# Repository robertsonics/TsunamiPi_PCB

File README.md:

# TsunamiPi_PCB
8-Out 2-In Multichannel Audio HAT

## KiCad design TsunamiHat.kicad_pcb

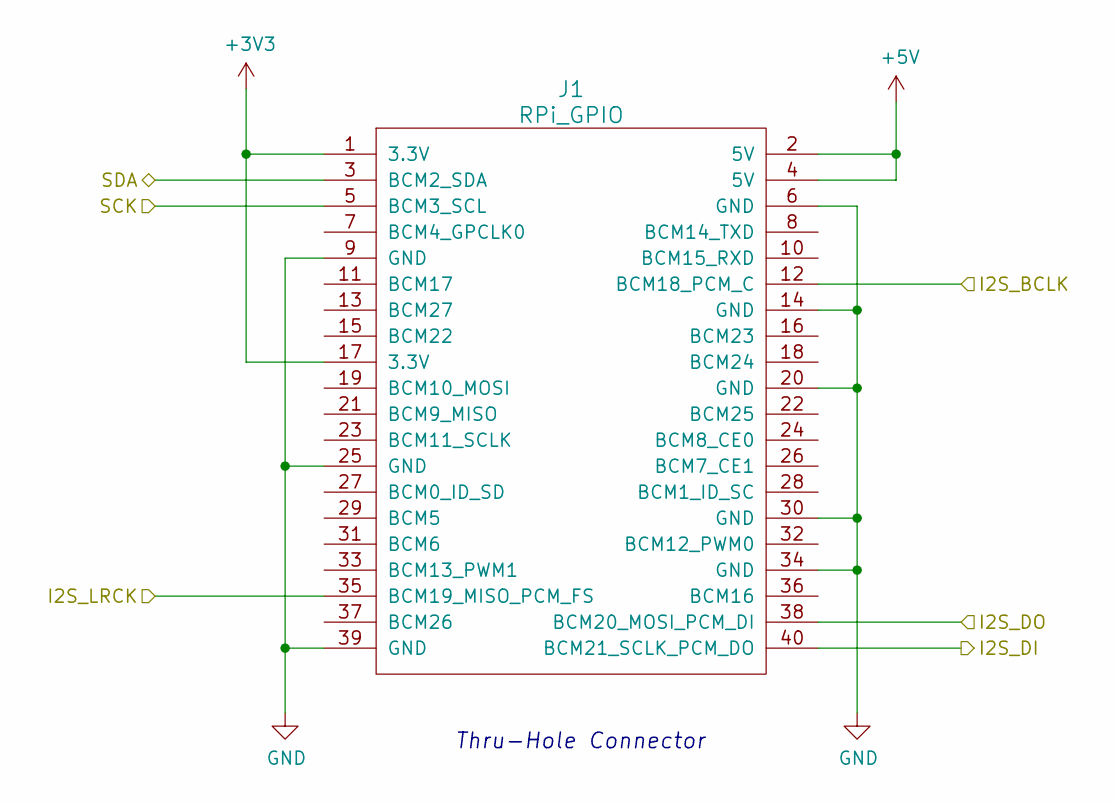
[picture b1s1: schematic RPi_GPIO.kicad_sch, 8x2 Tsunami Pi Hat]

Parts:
J1: RPi_GPIO; Pin_Header_Straight_2x20

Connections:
+3V3: J1.1 (3.3V), J1.17 (3.3V); also elsewhere on the board
+5V: J1.2 (5V), J1.4 (5V); also elsewhere on the board
/CPU/I2S_BCLK: J1.12 (BCM18_PCM_C); also elsewhere on the board
/CPU/I2S_DI: J1.40 (BCM21_SCLK_PCM_DO); also elsewhere on the board
/CPU/I2S_LRCK: J1.35 (BCM19_MISO_PCM_FS); also elsewhere on the board
/CPU/SCK: J1.5 (BCM3_SCL); also elsewhere on the board
/CPU/SDA: J1.3 (BCM2_SDA); also elsewhere on the board
/Codec/I2S_DO: J1.38 (BCM20_MOSI_PCM_DI); also elsewhere on the board
GND: J1.6 (GND), J1.9 (GND), J1.14 (GND), J1.20 (GND), J1.25 (GND), J1.30 (GND), J1.34 (GND), J1.39 (GND); also elsewhere on the board

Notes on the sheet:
Thru-Hole Connector

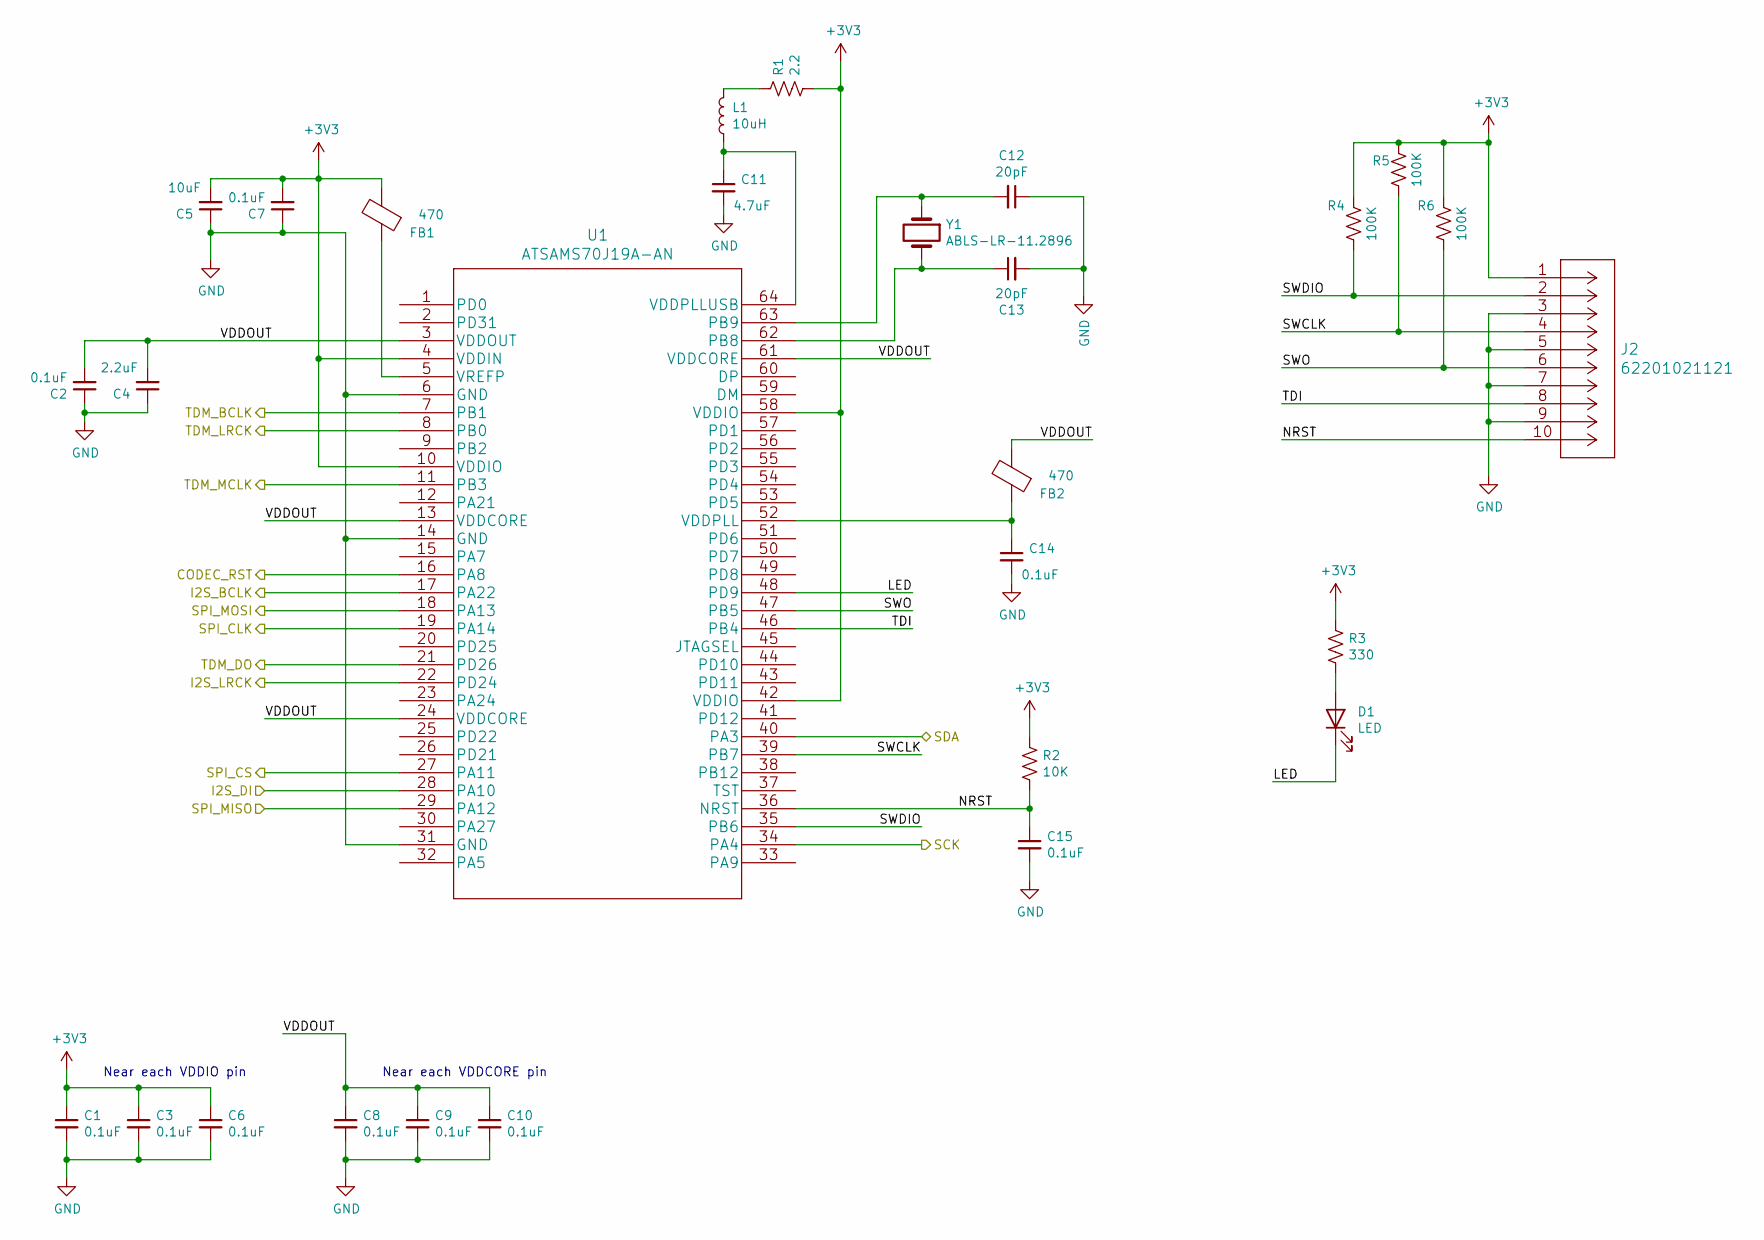
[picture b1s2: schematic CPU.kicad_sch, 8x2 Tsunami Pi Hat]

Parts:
C1, C2, C3, C6, C7, C8, C9, C10, C14, C15: 0.1uF; C_0603_1608Metric
C4: 2.2uF; C_0603_1608Metric
C5: 10uF; C_0805_2012Metric
C11: 4.7uF; C_0603_1608Metric
C12, C13: 20pF; C_0603_1608Metric
D1: LED; LED_0603_1608Metric
FB1, FB2: 470; L_0603_1608Metric
J2: 62201021121
L1: 10uH; L_0603_1608Metric
R1: 2.2; R_0603_1608Metric
R2: 10K; R_0603_1608Metric
R3: 330; R_0603_1608Metric
R4, R5, R6: 100K; R_0603_1608Metric
U1: ATSAMS70J19A-AN
Y1: ABLS-LR-11.2896; XTAL_ABLS-24.000MHZ-B4-T

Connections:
+3V3: C1.1, C3.1, C5.2, C6.1, C7.2, FB1.2, J2.1, R1.1, R2.2, R3.2, R4.2, R5.2, R6.2, U1.4 (VDDIN), U1.10 (VDDIO), U1.42 (VDDIO), U1.58 (VDDIO); also elsewhere on the board
/CPU/CODEC_RST: U1.16 (PA8); also elsewhere on the board
/CPU/I2S_BCLK: U1.17 (PA22); also elsewhere on the board
/CPU/I2S_DI: U1.28 (PA10); also elsewhere on the board
/CPU/I2S_LRCK: U1.22 (PD24); also elsewhere on the board
/CPU/LED: D1.1 (K), U1.48 (PD9)
/CPU/NRST: C15.1, J2.10, R2.1, U1.36 (NRST)
/CPU/SCK: U1.34 (PA4); also elsewhere on the board
/CPU/SDA: U1.40 (PA3); also elsewhere on the board
/CPU/SPI_CLK: U1.19 (PA14); also elsewhere on the board
/CPU/SPI_CS: U1.27 (PA11); also elsewhere on the board
/CPU/SPI_MISO: U1.29 (PA12); also elsewhere on the board
/CPU/SPI_MOSI: U1.18 (PA13); also elsewhere on the board
/CPU/SWCLK: J2.4, R5.1, U1.39 (PB7)
/CPU/SWDIO: J2.2, R4.1, U1.35 (PB6)
/CPU/SWO: J2.6, R6.1, U1.47 (PB5)
/CPU/TDI: J2.8, U1.46 (PB4)
/CPU/TDM_BCLK: U1.7 (PB1); also elsewhere on the board
/CPU/TDM_DO: U1.21 (PD26); also elsewhere on the board
/CPU/TDM_LRCK: U1.8 (PB0); also elsewhere on the board
/CPU/TDM_MCLK: U1.11 (PB3); also elsewhere on the board
/CPU/VDDOUT: C2.2, C4.2, C8.1, C9.1, C10.1, FB2.2, U1.3 (VDDOUT), U1.13 (VDDCORE), U1.24 (VDDCORE), U1.61 (VDDCORE)
GND: C1.2, C2.1, C3.2, C4.1, C5.1, C6.2, C7.1, C8.2, C9.2, C10.2, C11.2, C12.1, C13.2, C14.2, C15.2, J2.3, J2.5, J2.7, J2.9, U1.6 (GND), U1.14 (GND), U1.31 (GND); also elsewhere on the board
unnamed: C11.1, L1.1, U1.64 (VDDPLLUSB)
unnamed: C12.2, U1.63 (PB9), Y1.1
unnamed: C13.1, U1.62 (PB8), Y1.2
unnamed: C14.1, FB2.1, U1.52 (VDDPLL)
unnamed: D1.2 (A), R3.1
unnamed: FB1.1, U1.5 (VREFP)
unnamed: L1.2, R1.2

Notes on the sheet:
Near each VDDCORE pin
Near each VDDIO pin

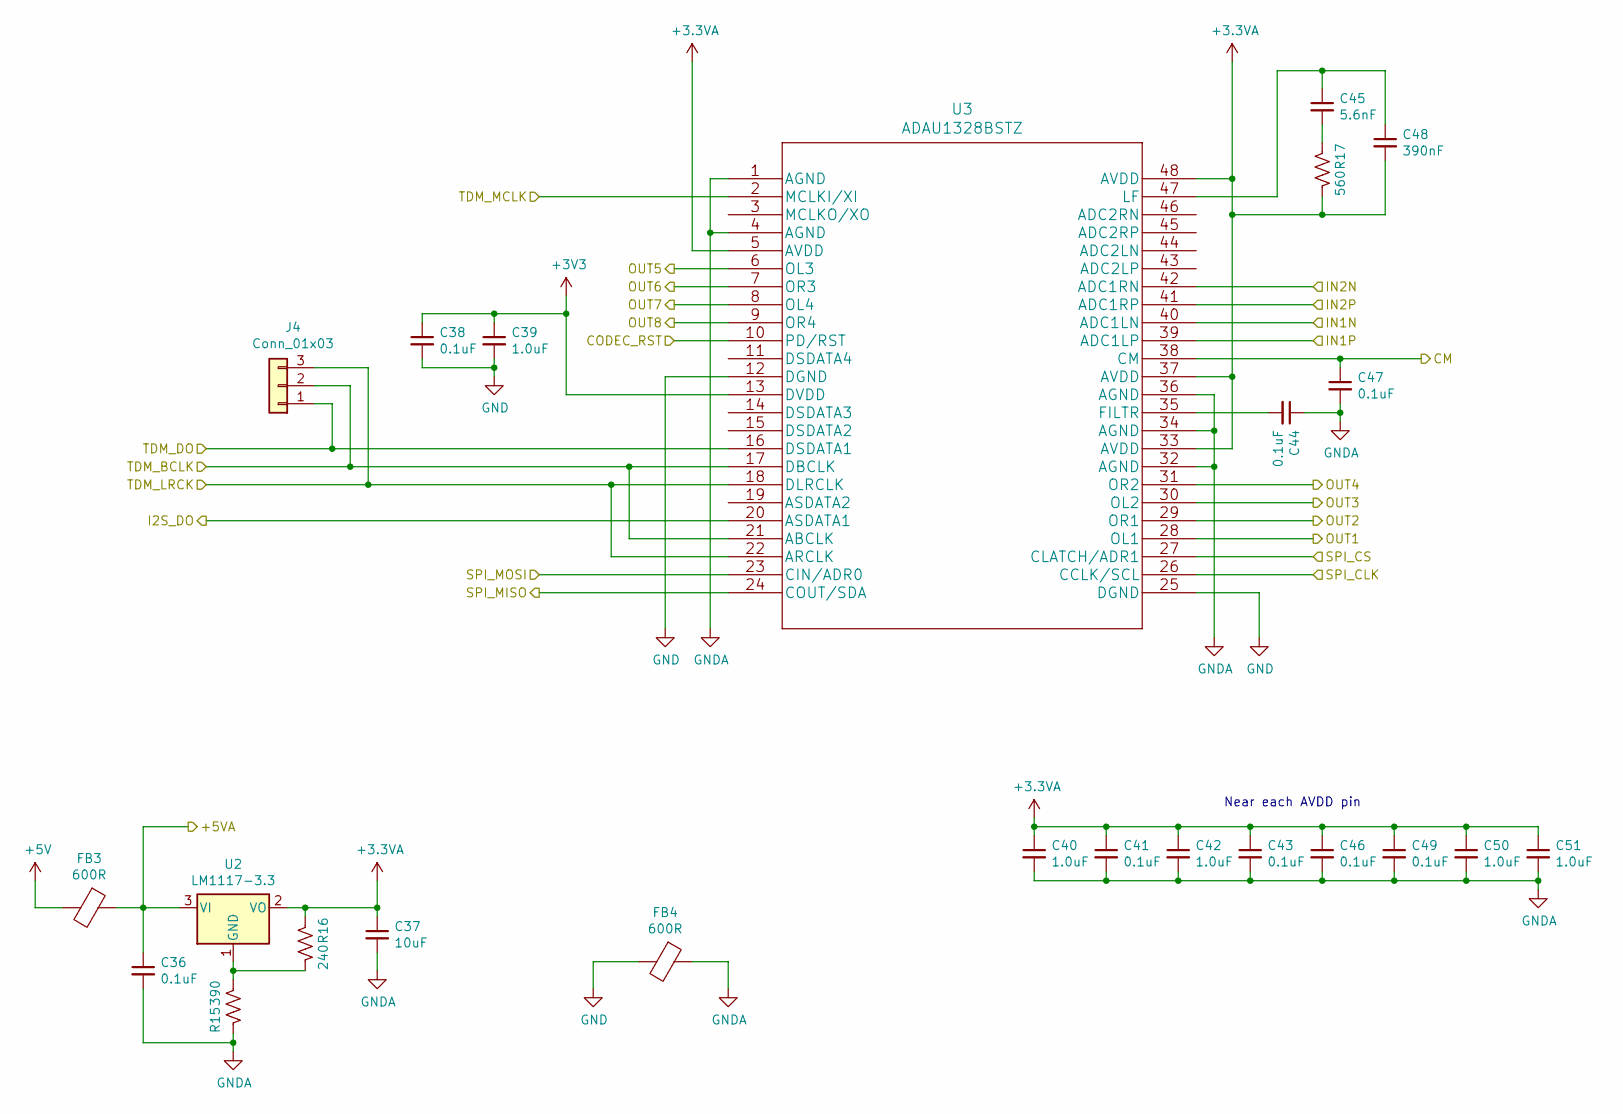
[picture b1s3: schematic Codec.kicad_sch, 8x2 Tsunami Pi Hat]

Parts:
C36, C38, C41, C43, C44, C46, C47, C49: 0.1uF; C_0603_1608Metric
C37: 10uF; C_0805_2012Metric
C39, C40, C42, C50, C51: 1.0uF; C_0603_1608Metric
C45: 5.6nF; C_0603_1608Metric
C48: 390nF; C_0603_1608Metric
FB3, FB4: 600R; L_0603_1608Metric
J4: Conn_01x03; PinHeader_1x03_P2.54mm_Vertical
R15: 390; R_0603_1608Metric
R16: 240; R_0603_1608Metric
R17: 560; R_0603_1608Metric
U2: LM1117-3.3; SOT-223-3_TabPin2; Mpn LM1117MP-3.3/NOPB
U3: ADAU1328BSTZ

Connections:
+3.3VA: C37.1, C40.1, C41.1, C42.1, C43.1, C46.1, C48.2, C49.1, C50.1, C51.1, R16.2, R17.1, U2.2 (VO), U3.5 (AVDD), U3.33 (AVDD), U3.37 (AVDD), U3.48 (AVDD); also elsewhere on the board
+3V3: C38.1, C39.1, U3.13 (DVDD); also elsewhere on the board
+5V: FB3.2; also elsewhere on the board
/AnalogIO/CM: C47.1, U3.38 (CM); also elsewhere on the board
/AnalogIO/IN1N: U3.40 (ADC1LN); also elsewhere on the board
/AnalogIO/IN1P: U3.39 (ADC1LP); also elsewhere on the board
/AnalogIO/IN2N: U3.42 (ADC1RN); also elsewhere on the board
/AnalogIO/IN2P: U3.41 (ADC1RP); also elsewhere on the board
/AnalogIO/OUT1: U3.28 (OL1); also elsewhere on the board
/AnalogIO/OUT2: U3.29 (OR1); also elsewhere on the board
/AnalogIO/OUT3: U3.30 (OL2); also elsewhere on the board
/AnalogIO/OUT4: U3.31 (OR2); also elsewhere on the board
/AnalogIO/OUT5: U3.6 (OL3); also elsewhere on the board
/AnalogIO/OUT6: U3.7 (OR3); also elsewhere on the board
/AnalogIO/OUT7: U3.8 (OL4); also elsewhere on the board
/AnalogIO/OUt8: U3.9 (OR4); also elsewhere on the board
/CPU/CODEC_RST: U3.10 (PD/RST); also elsewhere on the board
/CPU/SPI_CLK: U3.26 (CCLK/SCL); also elsewhere on the board
/CPU/SPI_CS: U3.27 (CLATCH/ADR1); also elsewhere on the board
/CPU/SPI_MISO: U3.24 (COUT/SDA); also elsewhere on the board
/CPU/SPI_MOSI: U3.23 (CIN/ADR0); also elsewhere on the board
/CPU/TDM_BCLK: J4.2, U3.17 (DBCLK), U3.21 (ABCLK); also elsewhere on the board
/CPU/TDM_DO: J4.1, U3.16 (DSDATA1); also elsewhere on the board
/CPU/TDM_LRCK: J4.3, U3.18 (DLRCLK), U3.22 (ARCLK); also elsewhere on the board
/CPU/TDM_MCLK: U3.2 (MCLKI/XI); also elsewhere on the board
/Codec/+5VA: C36.1, FB3.1, U2.3 (VI)
/Codec/I2S_DO: U3.20 (ASDATA1); also elsewhere on the board
GND: C38.2, C39.2, FB4.2, U3.12 (DGND), U3.25 (DGND); also elsewhere on the board
GNDA: C36.2, C37.2, C40.2, C41.2, C42.2, C43.2, C44.1, C46.2, C47.2, C49.2, C50.2, C51.2, FB4.1, R15.2, U3.1 (AGND), U3.4 (AGND), U3.32 (AGND), U3.34 (AGND), U3.36 (AGND); also elsewhere on the board
unnamed: C44.2, U3.35 (FILTR)
unnamed: C45.1, C48.1, U3.47 (LF)
unnamed: C45.2, R17.2
unnamed: R15.1, R16.1, U2.1 (GND)

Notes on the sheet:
Near each AVDD pin

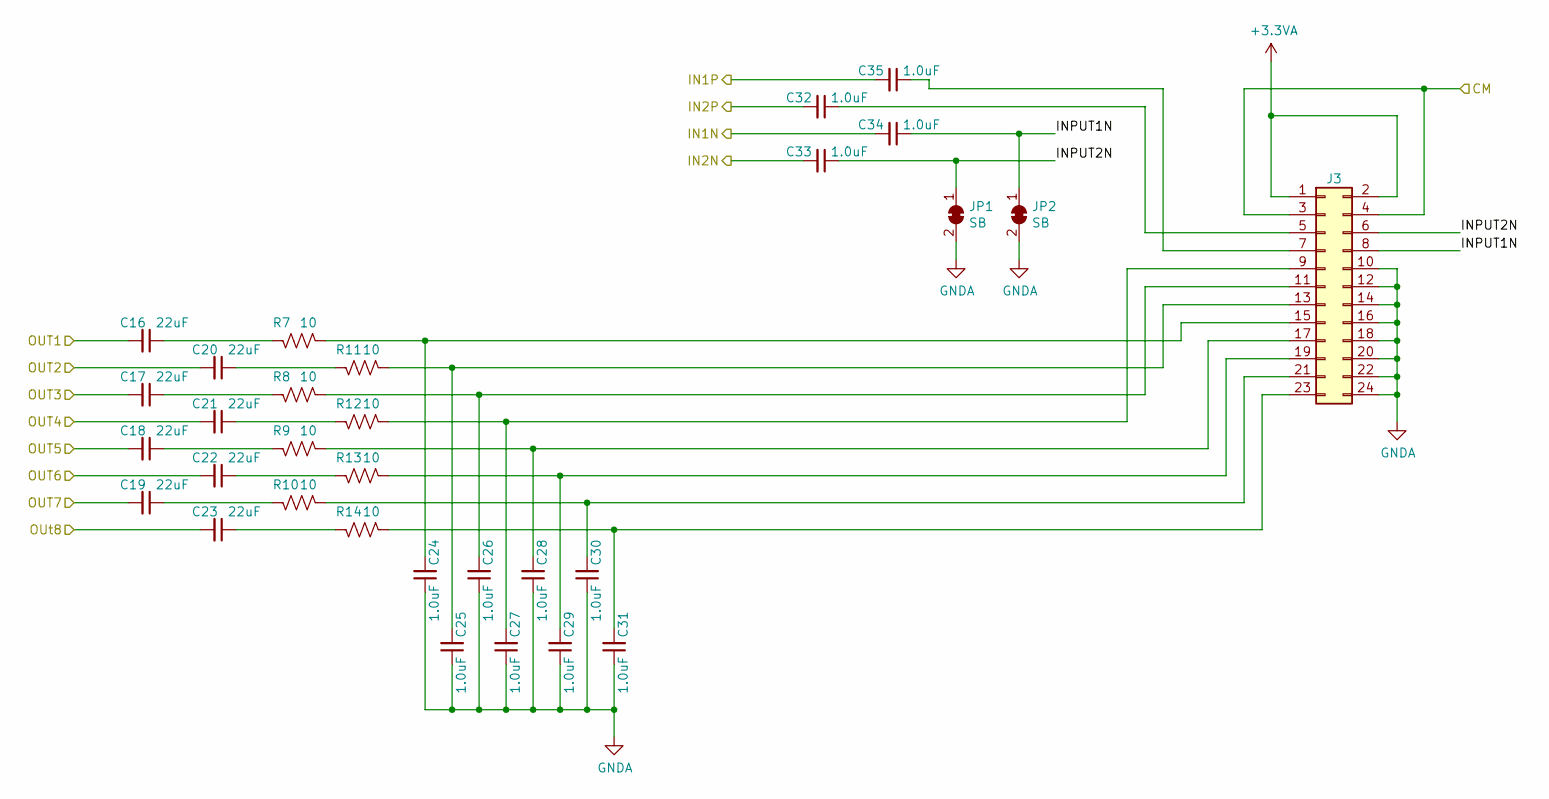
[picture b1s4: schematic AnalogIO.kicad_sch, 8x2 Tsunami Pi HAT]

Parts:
C16, C17, C18, C19, C20, C21, C22, C23: 22uF; C_0805_2012Metric
C24, C25, C26, C27, C28, C29, C30, C31, C32, C33, C34, C35: 1.0uF; C_0603_1608Metric
J3: Conn_02x12_Odd_Even; PinHeader_2x12_P2.54mm_Vertical
JP1, JP2: SB; SolderJumper-2_P1.3mm_Bridged_RoundedPad1.0x1.5mm
R7, R8, R9, R10, R11, R12, R13, R14: 10; R_0603_1608Metric

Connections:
+3.3VA: J3.1, J3.2; also elsewhere on the board
/AnalogIO/CM: J3.3, J3.4; also elsewhere on the board
/AnalogIO/IN1N: C34.2; also elsewhere on the board
/AnalogIO/IN1P: C35.2; also elsewhere on the board
/AnalogIO/IN2N: C33.2; also elsewhere on the board
/AnalogIO/IN2P: C32.2; also elsewhere on the board
/AnalogIO/INPUT1N: C34.1, J3.8, JP2.1 (A)
/AnalogIO/INPUT2N: C33.1, J3.6, JP1.1 (A)
/AnalogIO/OUT1: C16.2; also elsewhere on the board
/AnalogIO/OUT2: C20.2; also elsewhere on the board
/AnalogIO/OUT3: C17.2; also elsewhere on the board
/AnalogIO/OUT4: C21.2; also elsewhere on the board
/AnalogIO/OUT5: C18.2; also elsewhere on the board
/AnalogIO/OUT6: C22.2; also elsewhere on the board
/AnalogIO/OUT7: C19.2; also elsewhere on the board
/AnalogIO/OUt8: C23.2; also elsewhere on the board
GNDA: C24.1, C25.1, C26.1, C27.1, C28.1, C29.1, C30.1, C31.1, J3.10, J3.12, J3.14, J3.16, J3.18, J3.20, J3.22, J3.24, JP1.2 (B), JP2.2 (B); also elsewhere on the board
unnamed: C16.1, R7.2
unnamed: C17.1, R8.2
unnamed: C18.1, R9.2
unnamed: C19.1, R10.2
unnamed: C20.1, R11.2
unnamed: C21.1, R12.2
unnamed: C22.1, R13.2
unnamed: C23.1, R14.2
unnamed: C24.2, J3.15, R7.1
unnamed: C25.2, J3.13, R11.1
unnamed: C26.2, J3.11, R8.1
unnamed: C27.2, J3.9, R12.1
unnamed: C28.2, J3.17, R9.1
unnamed: C29.2, J3.19, R13.1
unnamed: C30.2, J3.21, R10.1
unnamed: C31.2, J3.23, R14.1
unnamed: C32.1, J3.5
unnamed: C35.1, J3.7

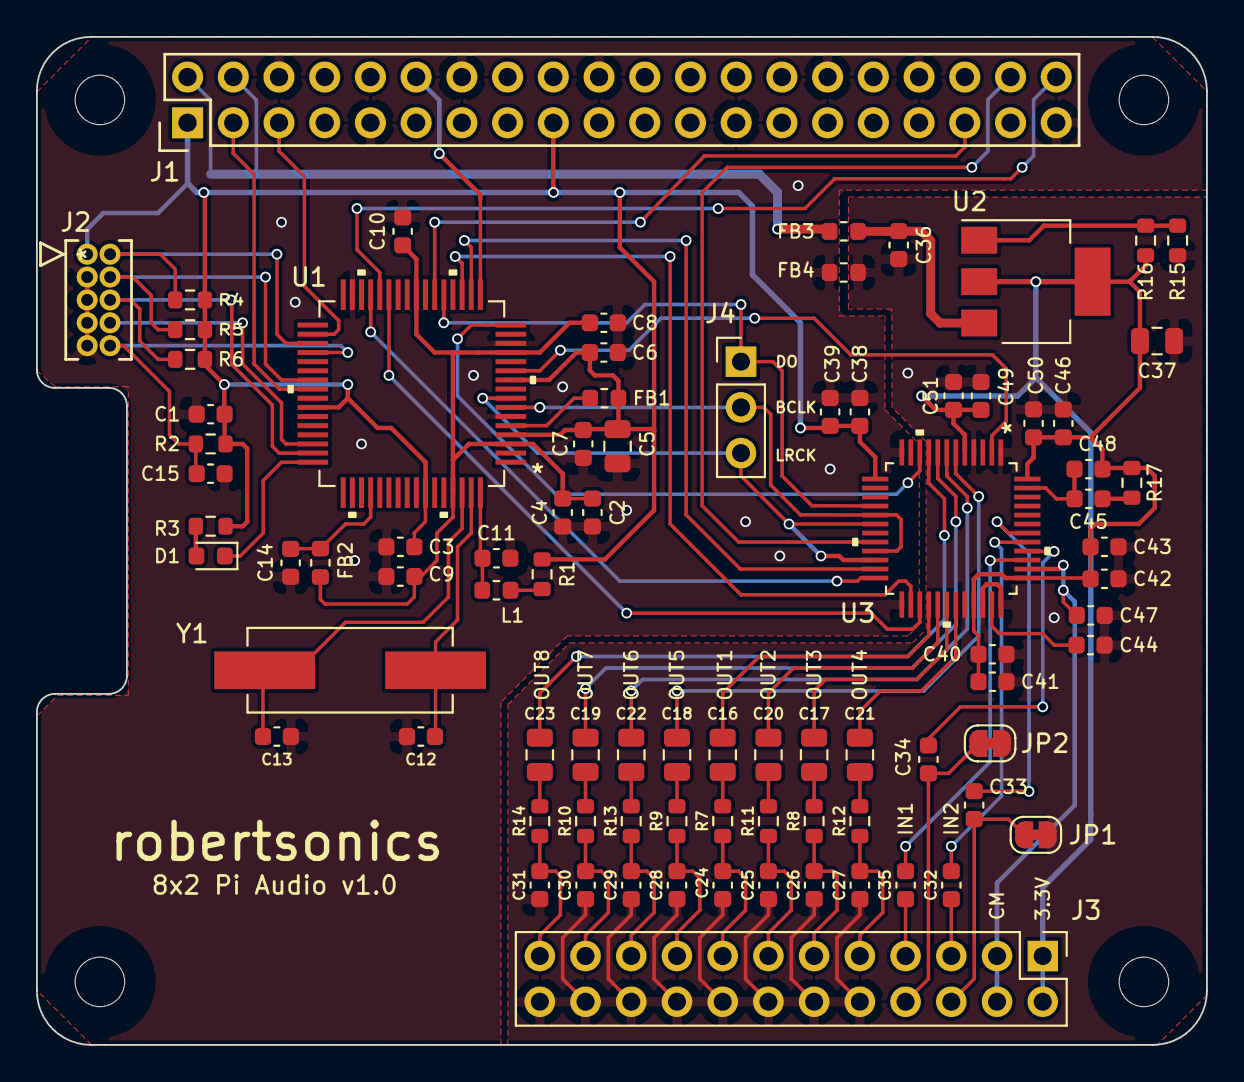
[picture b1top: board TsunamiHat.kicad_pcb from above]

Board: 2 copper layers, 65.0 x 56.0 mm, 84 parts (0 on the bottom side), 72 nets.

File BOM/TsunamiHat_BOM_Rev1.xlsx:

Item # | Quantity Per Board | Manufacturer Part # | Manufacturer | Do Not Install | Reference | Vendor | Vendor Part # | Value | Footprint
1 | 1 | CC0603MRX5R6BB475 |  |  | C11 | Digikey | 311-1820-1-ND | 4.7uF | 0603_1608Metric
2 | 2 | CBR06C200FAGAC |  |  | C12 C13 | Digikey | 399-8840-1-ND | 20pF | 0603_1608Metric
3 | 18 | C0603C104K9PAC7867 |  |  | C1 C2 C3 C6 C7 C8 C9 C10 C14 C15 C36 C38 C41 C43 C44 C46 C47 C49 | Digikey | 399-17575-1-ND | 0.1uF | 0603_1608Metric
4 | 8 | TACR226K006XTA |  |  | C16 C17 C18 C19 C20 C21 C22 C23 | Digikey | 478-4188-1-ND | 22uF | 0805_2012Metric
5 | 17 | C0603C105K4PACTU |  |  | C24 C25 C26 C27 C28 C29 C30 C31 C32 C33 C34 C35 C39 C40 C42 C50 C51 | Digikey | 399-5090-1-ND | 1.0uF | 0603_1608Metric
6 | 1 | C0603C225K8PACTU |  |  | C4 | Digikey | 399-4911-1-ND | 2.2uF | 0603_1608Metric
7 | 1 | 06035C562JAT2A |  |  | C45 | Digikey | 478-12728-1-ND | 5.6nF | 0603_1608Metric
8 | 1 | C0603C394J4RAC7867 |  |  | C48 | Digikey | 399-17256-1-ND | 390nF | 0603_1608Metric
9 | 2 | CC0805KRX5R6BB106 |  |  | C5 C37 | Digikey | 311-3424-1-ND | 10uF | 0805_2012Metric
10 | 1 | LTST-C191TBKT | LITEON |  | D1 | Digikey | 160-1647-1-ND | LED | 0603_1608Metric
11 | 2 | FBMH1608HL471-T | Taiyo Yuden |  | FB1 FB2 | Digikey | 587-1735-1-ND | 470 | 0603_1608Metric
12 | 2 | KPZ1608SHR601ATD25 | TDK Corp |  | FB3 FB4 | Digikey | 445-175020-1-ND | 600 | 0603_1608Metric
13 | 1 |  |  | DNI | J1 |  |  | Conn_02x20 | PinHeader_2x20_P2.54mm_Vertical
14 | 1 |  |  | DNI | J2 |  |  | 62201021121 | JTAG-header:62201021121
15 | 1 |  |  | DNI | J3 |  |  | Conn_02x12 | PinHeader_2x12_P2.54mm_Vertical
16 | 1 |  |  | DNI | J4 |  |  | Conn_01x03 | PinHeader_1x03_P2.54mm_Vertical
17 | 1 | MLZ1608M100WTD25 | TDK Corp |  | L1 | Digikey | 445-175588-1-ND | 10uH | 0603_1608Metric
18 | 1 | RMCF0603FT2R20 |  |  | R1 | Digikey | RMCF0603FT2R20CT-ND | 2.2000000000000002 | 0603_1608Metric
19 | 8 | RMCF0603JT10R0 |  |  | R7 R8 R9 R10 R11 R12 R13 R14 | Digikey | RMCF0603JT10R0CT-ND | 10 | 0603_1608Metric
20 | 1 | RMCF0603FT390R |  |  | R15 | Digikey | RMCF0603FT390RCT-ND | 390 | 0603_1608Metric
21 | 1 | RMCF0603FT240R |  |  | R16 | Digikey | 738-RMCF0603FT240RCT-ND | 240 | 0603_1608Metric
22 | 1 | RMCF0603FT560R |  |  | R17 | Digikey | 738-RMCF0603FT560RCT-ND | 560 | 0603_1608Metric
23 | 1 | RMCF0603FT10K0 |  |  | R2 | Digikey | RMCF0603FT10K0CT-ND | 10K | 0603_1608Metric
24 | 1 | RMCF0603FT330R |  |  | R3 | Digikey | RMCF0603FT330RCT-ND | 330 | 0603_1608Metric
25 | 3 | RMCF0603FT100K |  |  | R4 R5 R6 | Digikey | RMCF0603FT100KCT-ND | 100K | 0603_1608Metric
26 | 1 | ATSAMS70J19A-AN | Microchip |  | U1 | Arrow | ATSAMS70J19A-AN | ATSAMS70J19A-AN | LQFP-64
27 | 1 | LM1117IMP-ADJ | National Semi |  | U2 | Rochester | LM1117IMP-ADJ | LM1117 | SOT-223-4
28 | 1 | ADAU1328BSTZ | Analog Devices |  | U3 | Rochester | ADAU1328BSTZ | ADAU1328BSTZ | LQFP-48
29 | 1 | 9C-11.2896MAAJ-T | TXC Corp |  | Y1 | Digikey | 887-1052-1-ND | ABLS-LR-11.2896 | HC/49-US

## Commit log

2022-01-14 Initial repo upload. Version used for initial 5-piece order from PCBWay.

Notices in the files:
parts and their libraries:
Copyright 2016 Accelerated Designs. All rights reserved.
Copyright 2021 Accelerated Designs. All rights reserved.
